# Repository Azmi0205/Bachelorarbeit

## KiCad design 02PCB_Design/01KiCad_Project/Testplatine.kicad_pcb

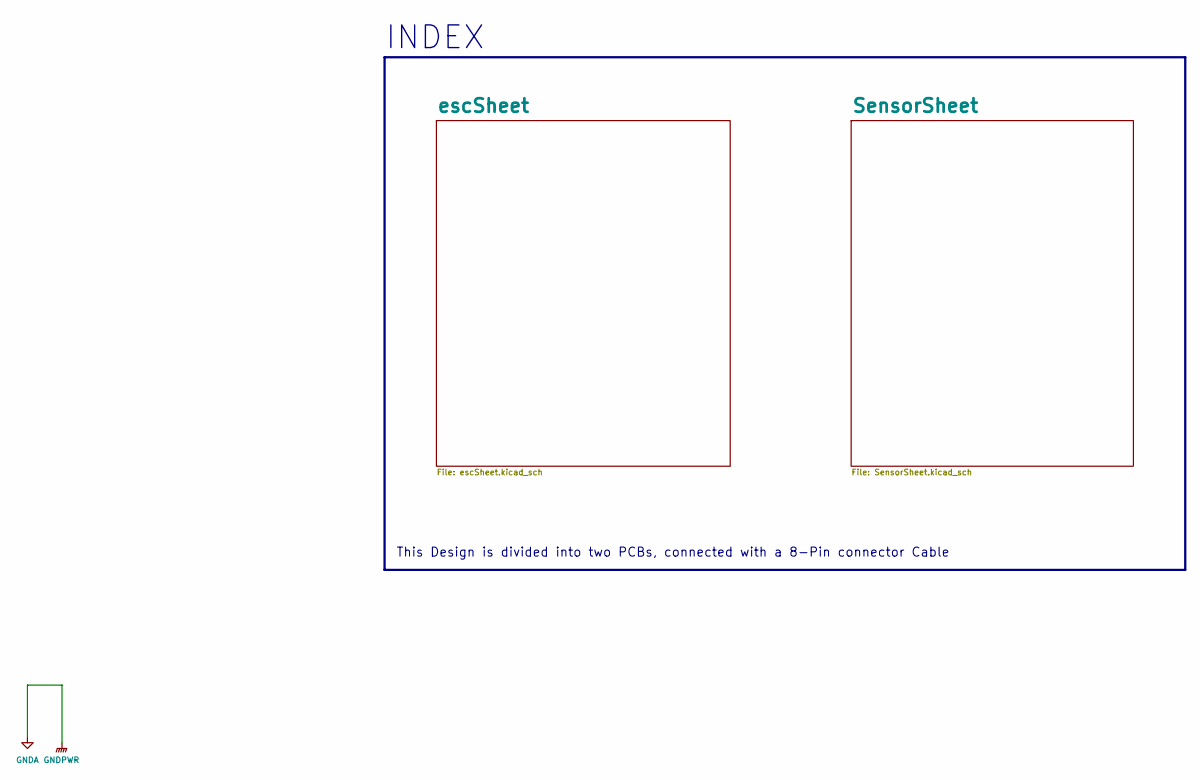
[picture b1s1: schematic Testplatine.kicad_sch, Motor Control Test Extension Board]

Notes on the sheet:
This Design is divided into two PCBs, connected with a 8-Pin connector Cable
INDEX

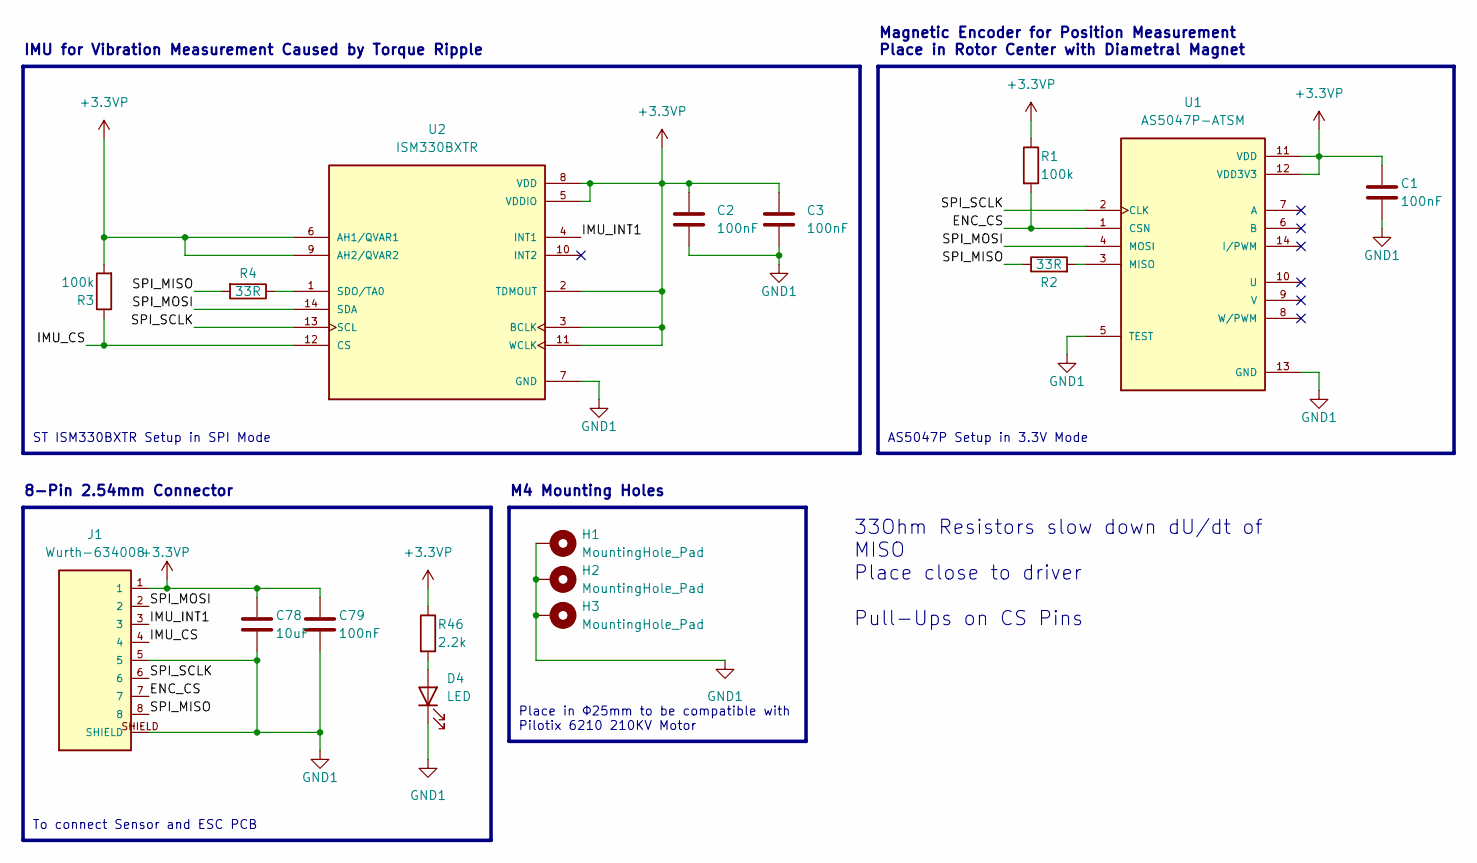
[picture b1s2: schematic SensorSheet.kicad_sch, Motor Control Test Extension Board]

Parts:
C1, C2, C3, C79: 100nF; C_0603_1608Metric_Pad1.08x0.95mm_HandSolder
C78: 10uF; C_1210_3225Metric_Pad1.33x2.70mm_HandSolder
D4: LED; LED_0805_2012Metric_Pad1.15x1.40mm_HandSolder
H1, H2, H3: MountingHole_Pad; MountingHole_4.3mm_M4_Pad_Via
J1: Wurth-634008; Wurth_634008_RJ45; PARTREV G
R1, R3: 100k; R_0603_1608Metric_Pad0.98x0.95mm_HandSolder
R2, R4: 33R; R_0603_1608Metric_Pad0.98x0.95mm_HandSolder
R46: 2.2k; R_0805_2012Metric_Pad1.20x1.40mm_HandSolder
U1: AS5047P-ATSM; TSSOP-14_4.4x5mm_P0.65mm; PARTREV 1-01
U2: ISM330BXTR; LGA-14_3x2.5mm_P0.5mm_LayoutBorder3x4y; PARTREV 2

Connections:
+3.3VP: C1.1, C2.1, C3.1, C78.1, C79.1, J1.1, R1.1, R3.2, R46.1, U1.11 (VDD), U1.12 (VDD3V3), U2.2 (TDMOUT), U2.3 (BCLK), U2.5 (VDDIO), U2.6 (AH1/QVAR1), U2.8 (VDD), U2.9 (AH2/QVAR2), U2.11 (WCLK)
/SensorSheet/ENC_CS: J1.7, R1.2, U1.1 (CSN)
/SensorSheet/IMU_CS: J1.4, R3.1, U2.12 (CS)
/SensorSheet/IMU_INT1: J1.3, U2.4 (INT1)
/SensorSheet/SPI_MISO: J1.8, R2.1, R4.2
/SensorSheet/SPI_MOSI: J1.2, U1.4 (MOSI), U2.14 (SDA)
/SensorSheet/SPI_SCLK: J1.6, U1.2 (CLK), U2.13 (SCL)
GND1: C1.2, C2.2, C3.2, C78.2, C79.2, D4.1 (K), H1.1, H2.1, H3.1, J1.5, J1.SHIELD, U1.5 (TEST), U1.13 (GND), U2.7 (GND)
unnamed: D4.2 (A), R46.2
unnamed: R2.2, U1.3 (MISO)
unnamed: R4.1, U2.1 (SDO/TA0)

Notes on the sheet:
33Ohm Resistors slow down dU/dt of MISO Place close to driver Pull-Ups on CS Pins
AS5047P Setup in 3.3V Mode
Place in Φ25mm to be compatible with Pilotix 6210 210KV Motor
8-Pin 2.54mm Connector
IMU for Vibration Measurement Caused by Torque Ripple
Magnetic Encoder for Position Measurement Place in Rotor Center with Diametral Magnet
To connect Sensor and ESC PCB
ST ISM330BXTR Setup in SPI Mode
M4 Mounting Holes

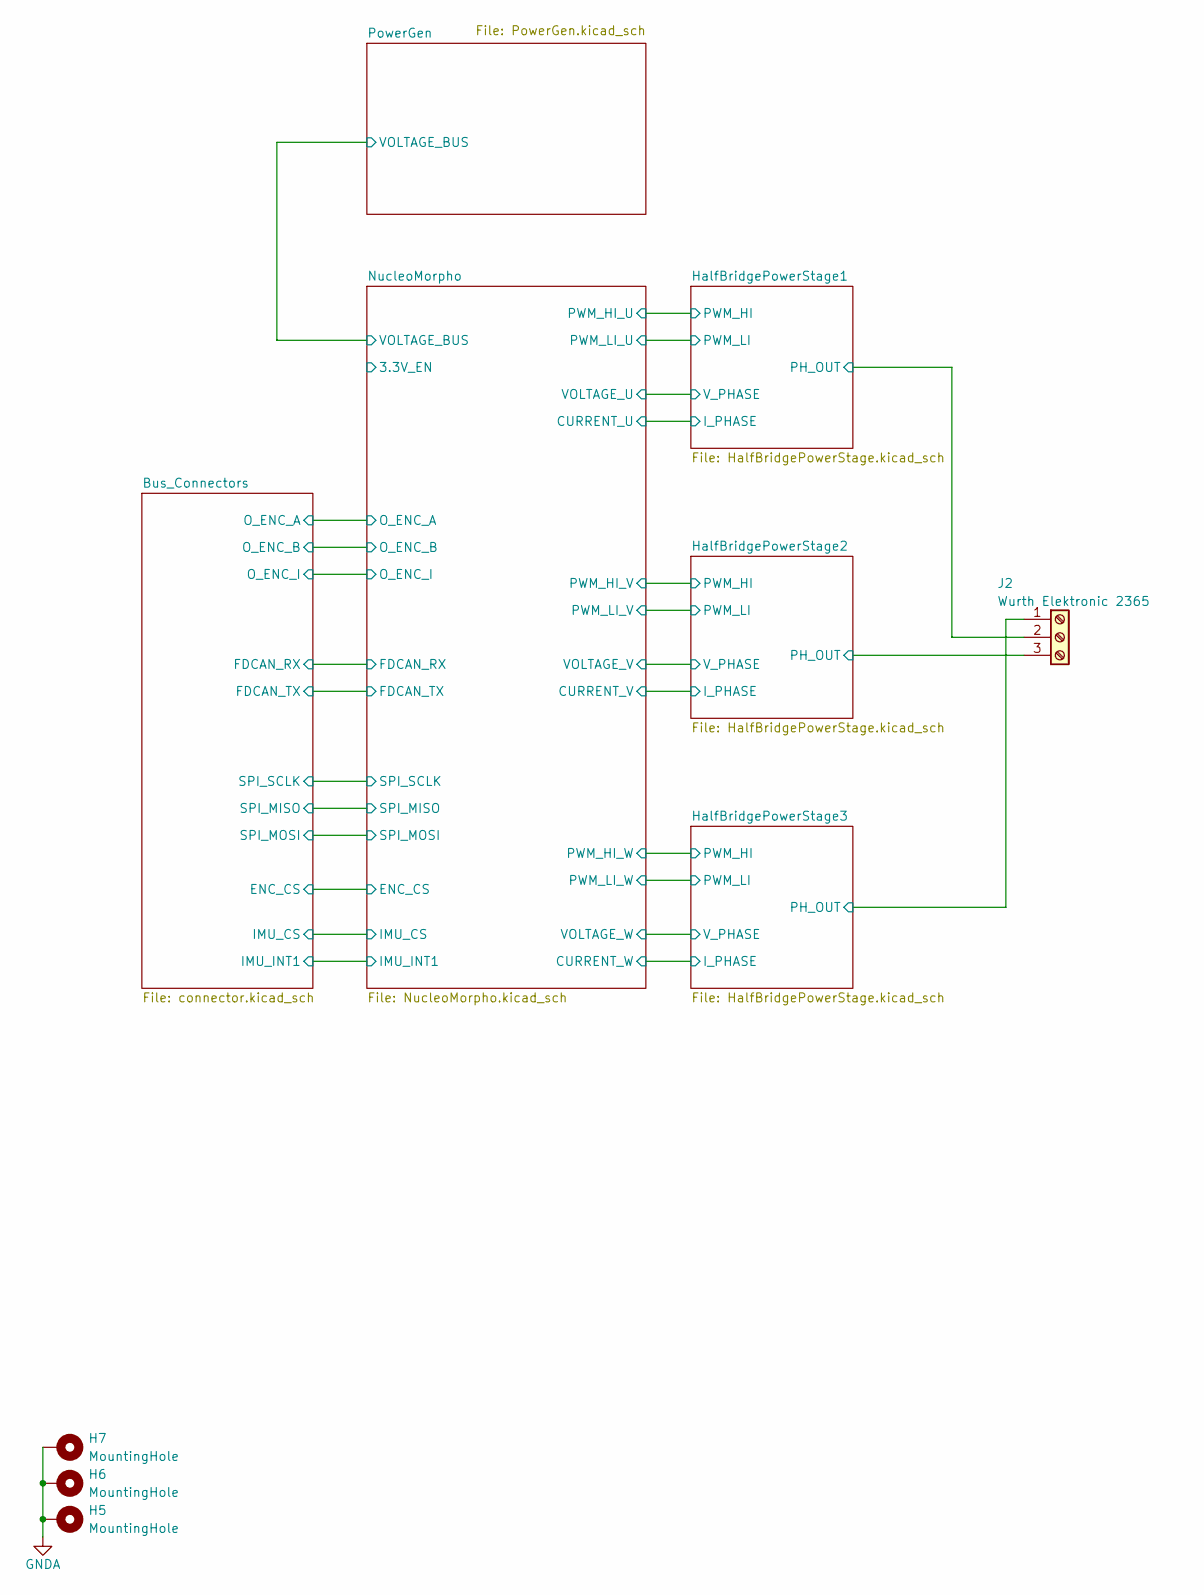
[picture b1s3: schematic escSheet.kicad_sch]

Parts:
H5, H6, H7: MountingHole; MountingHole_4.3mm_M4_Pad_Via
J2: Wurth Elektronic 2365; Wurth Elektronik 2365 Printklemme

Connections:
/escSheet/HalfBridgePowerStage1/PH_OUT: J2.2; also elsewhere on the board
/escSheet/HalfBridgePowerStage2/PH_OUT: J2.3; also elsewhere on the board
/escSheet/HalfBridgePowerStage3/PH_OUT: J2.1; also elsewhere on the board

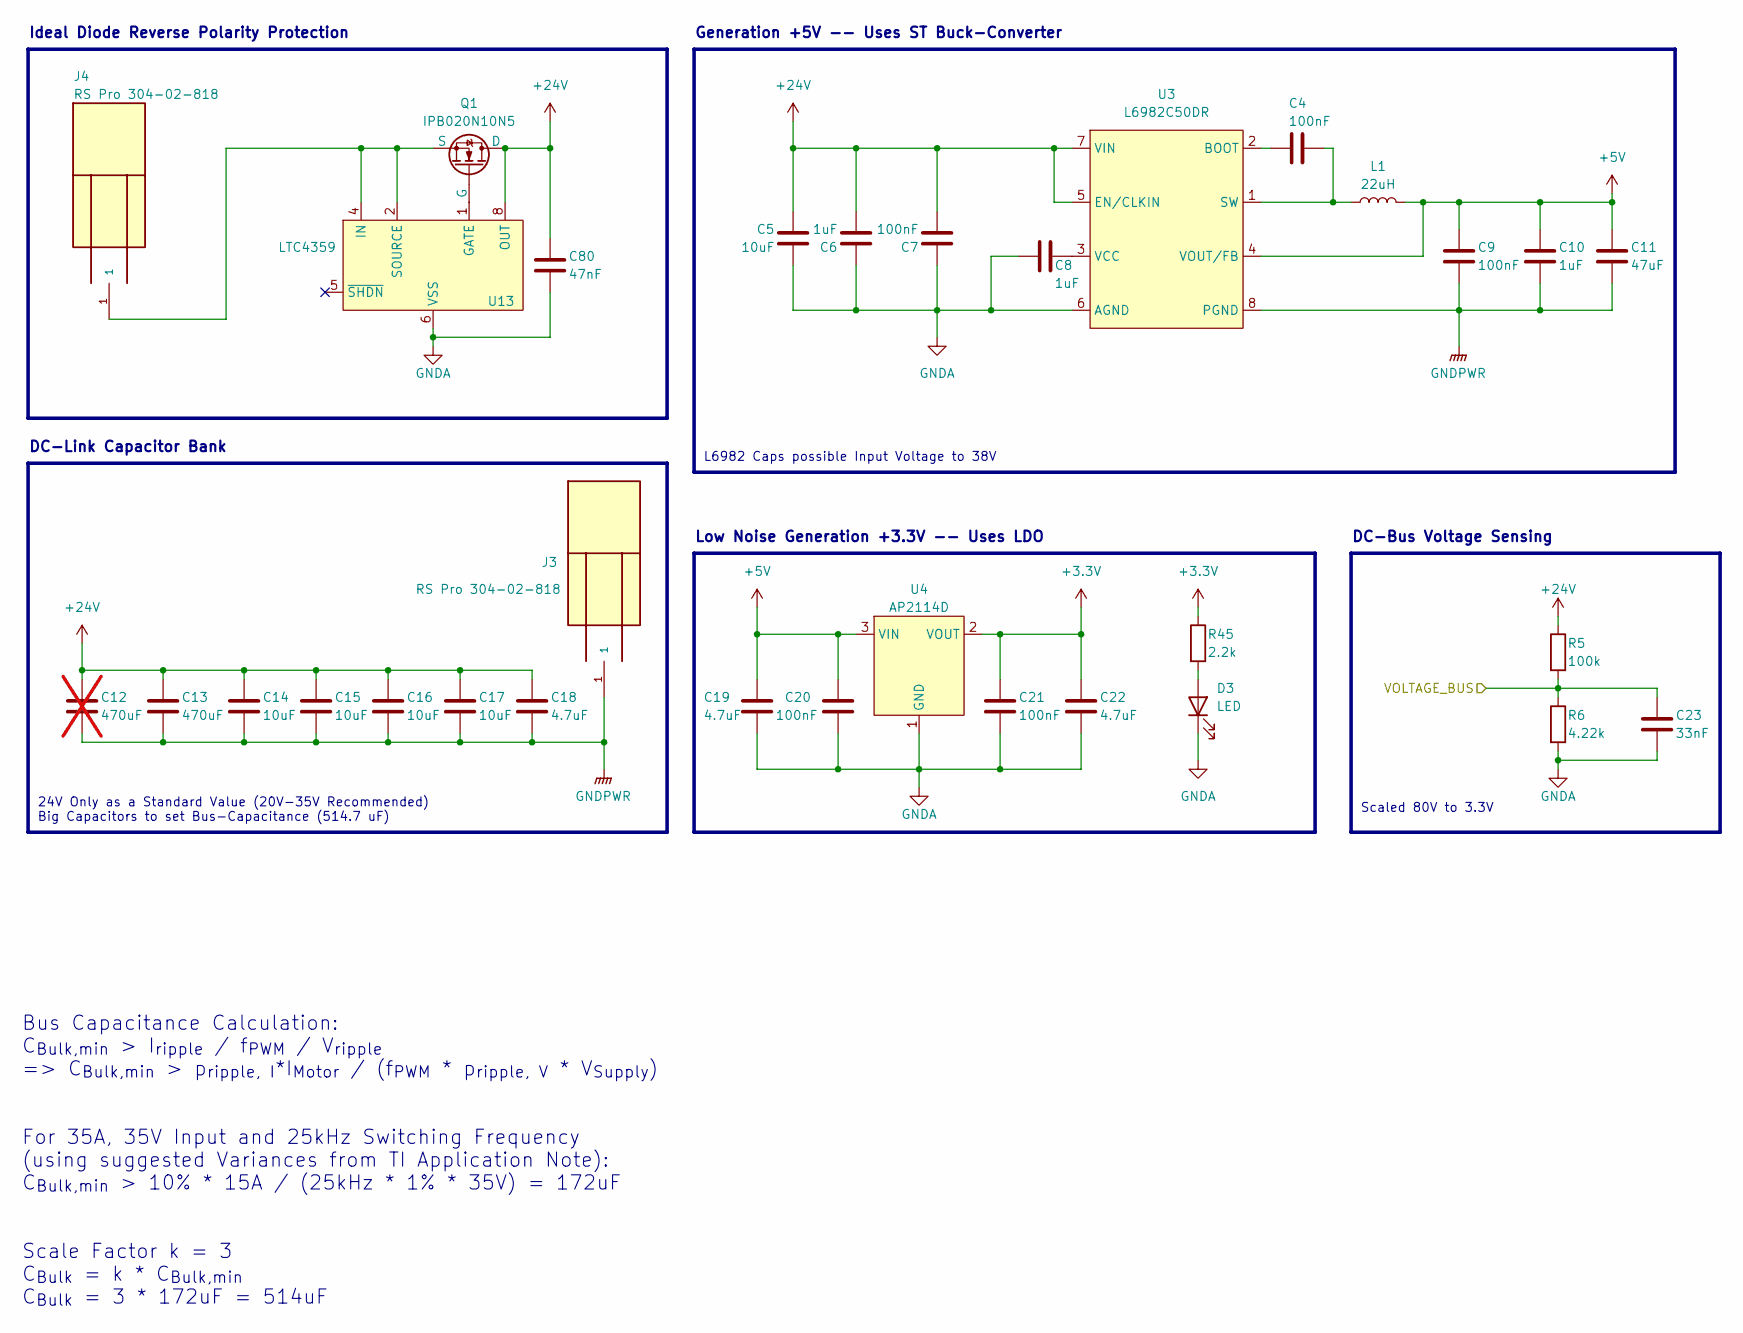
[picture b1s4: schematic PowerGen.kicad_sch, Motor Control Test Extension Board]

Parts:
C4, C7, C9, C20, C21: 100nF; C_0603_1608Metric_Pad1.08x0.95mm_HandSolder
C5, C14, C15, C16, C17: 10uF; C_1210_3225Metric_Pad1.33x2.70mm_HandSolder
C6, C8, C10: 1uF; C_0805_2012Metric_Pad1.18x1.45mm_HandSolder
C11: 47uF; C_1210_3225Metric_Pad1.33x2.70mm_HandSolder
C12: 470uF; CP_Radial_D16.0mm_P7.50mm; not fitted
C13: 470uF; CP_Radial_D16.0mm_P7.50mm
C18, C19, C22: 4.7uF; C_0805_2012Metric_Pad1.18x1.45mm_HandSolder
C23: 33nF; C_0603_1608Metric_Pad1.08x0.95mm_HandSolder
C80: 47nF; C_0603_1608Metric_Pad1.08x0.95mm_HandSolder
D3: LED; LED_0805_2012Metric_Pad1.15x1.40mm_HandSolder
J3, J4: RS Pro 304-02-818; FCR7350
L1: 22uH; L_Wuerth_MAPI-4020
Q1: IPB020N10N5; TO-263-2
R5: 100k; R_0603_1608Metric_Pad0.98x0.95mm_HandSolder
R6: 4.22k; R_0603_1608Metric_Pad0.98x0.95mm_HandSolder
R45: 2.2k; R_0805_2012Metric_Pad1.20x1.40mm_HandSolder
U3: L6982C50DR; SO-8_3.9x4.9mm_P1.27mm
U4: AP2114D; TO-252-2
U13: LTC4359; SO-8_3.9x4.9mm_P1.27mm

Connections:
+3.3V: C21.1, C22.1, R45.1, U4.2 (VOUT); also elsewhere on the board
+5V: C9.1, C10.1, C11.1, C19.1, C20.1, L1.2, U3.4 (VOUT/FB), U4.3 (VIN); also elsewhere on the board
+24V: C5.1, C6.2, C7.2, C12.1, C13.1, C14.1, C15.1, C16.1, C17.1, C18.1, C80.1, Q1.D, R5.1, U3.5 (EN/CLKIN), U3.7 (VIN), U13.8 (OUT); also elsewhere on the board
/escSheet/NucleoMorpho/VOLTAGE_BUS: C23.1, R5.2, R6.1; also elsewhere on the board
unnamed: D3.2 (A), R45.2
unnamed: C4.2, U3.2 (BOOT)
unnamed: C4.1, L1.1, U3.1 (SW)
unnamed: C8.1, U3.3 (VCC)
unnamed: Q1.G, U13.1 (GATE)
unnamed: J4.1, Q1.S, U13.2 (SOURCE), U13.4 (IN)

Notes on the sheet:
Bus Capacitance Calculation: C_{Bulk,min} > I_{ripple} / f_{PWM} / V_{ripple} => C_{Bulk,min} > p_{ripple, I}*I_{Motor} / (f_{PWM} * p_{ripple, V} * V_{Supply}) For 35A, 35V Input and 25kHz Switching Frequency (using suggested Variances from TI Application Note): C_{Bulk,min} > 10% * 15A / (25kHz *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
Scaled 80V to 3.3V
DC-Bus Voltage Sensing
Ideal Diode Reverse Polarity Protection
Low Noise Generation +3.3V -- Uses LDO
DC-Link Capacitor Bank
24V Only as a Standard Value (20V-35V Recommended) Big Capacitors to set Bus-Capacitance (514.7 uF)
L6982 Caps possible Input Voltage to 38V
Generation +5V -- Uses ST Buck-Converter

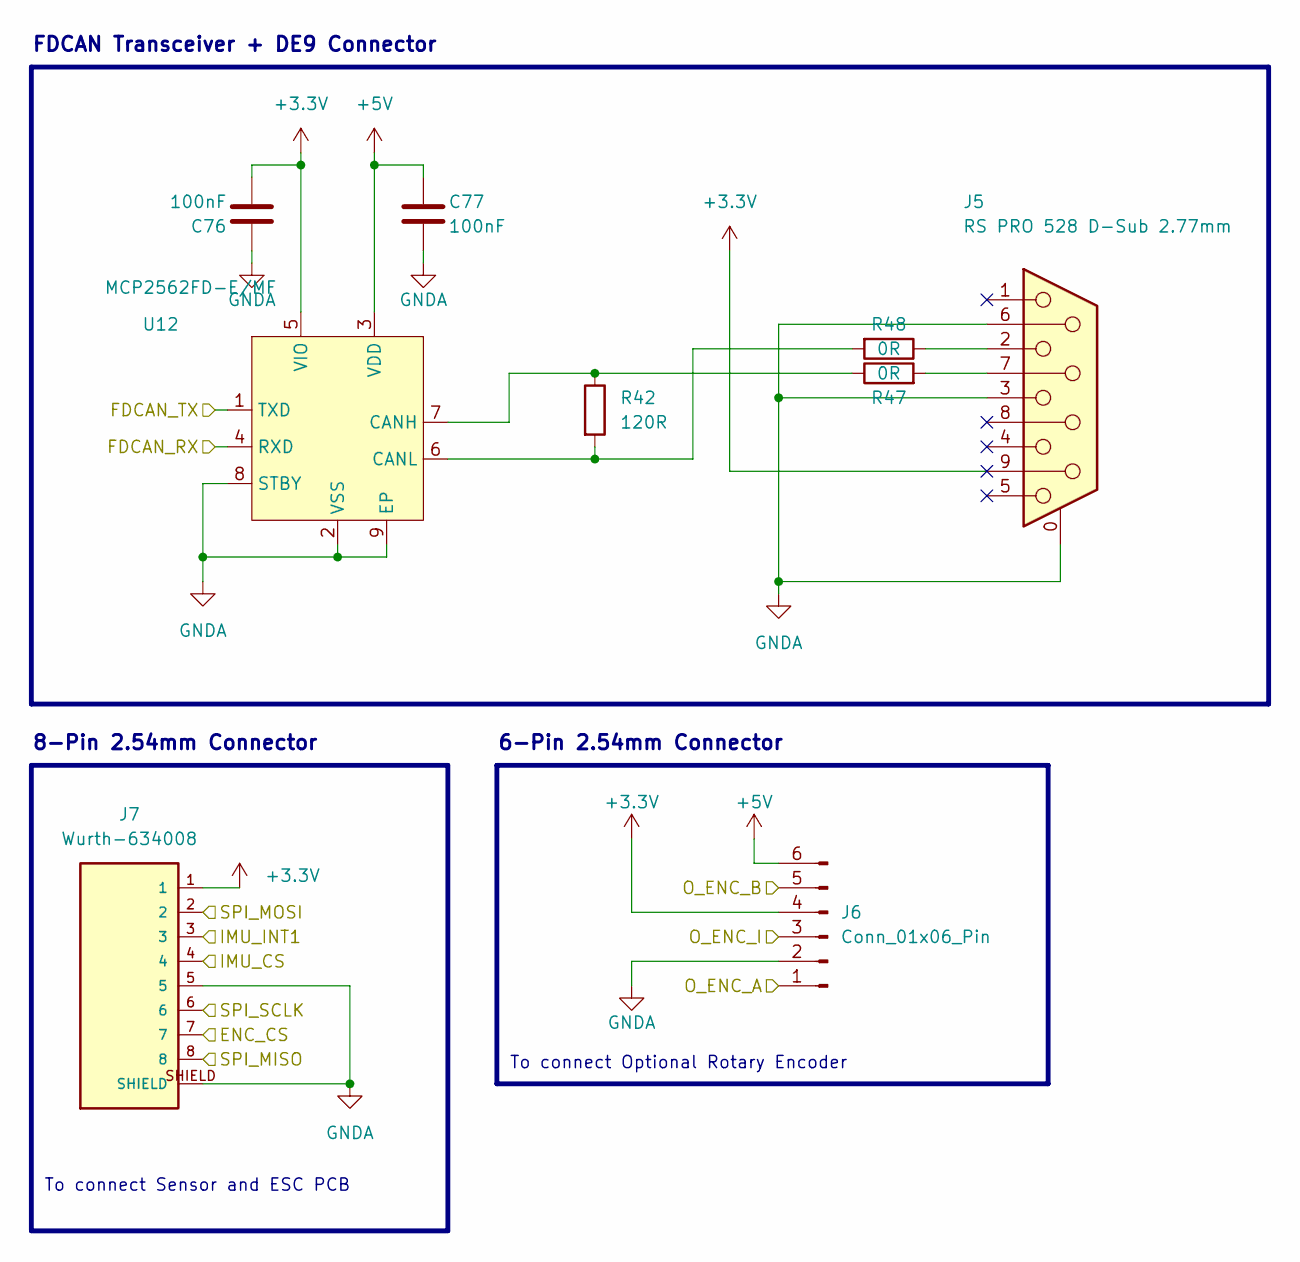
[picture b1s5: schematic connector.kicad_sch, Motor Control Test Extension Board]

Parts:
C76, C77: 100nF; C_0603_1608Metric_Pad1.08x0.95mm_HandSolder
J5: RS PRO 528 D-Sub 2.77mm; DSUB-9_Female_Horizontal_P2.77x2.84mm_EdgePinOffset4.94mm_H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
J6: Conn_01x06_Pin; PinHeader_2x03_P2.54mm_Horizontal
J7: Wurth-634008; Wurth_634008_RJ45; PARTREV G
R42: 120R; R_0603_1608Metric_Pad0.98x0.95mm_HandSolder
R47, R48: 0R; R_0603_1608Metric_Pad0.98x0.95mm_HandSolder
U12: MCP2562FD-E/MF; DFN-8-1EP_3x3mm_P0.65mm_EP1.55x2.4mm

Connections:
+3.3V: C76.2, J5.9, J6.4, J7.1, U12.5 (VIO); also elsewhere on the board
+5V: C77.1, J6.6, U12.3 (VDD); also elsewhere on the board
/escSheet/Bus_Connectors/ENC_CS: J7.7; also elsewhere on the board
/escSheet/Bus_Connectors/FDCAN_RX: U12.4 (RXD); also elsewhere on the board
/escSheet/Bus_Connectors/FDCAN_TX: U12.1 (TXD); also elsewhere on the board
/escSheet/Bus_Connectors/IMU_CS: J7.4; also elsewhere on the board
/escSheet/Bus_Connectors/IMU_INT1: J7.3; also elsewhere on the board
/escSheet/Bus_Connectors/O_ENC_A: J6.1; also elsewhere on the board
/escSheet/Bus_Connectors/O_ENC_B: J6.5; also elsewhere on the board
/escSheet/Bus_Connectors/O_ENC_I: J6.3; also elsewhere on the board
/escSheet/Bus_Connectors/SPI_MISO: J7.8; also elsewhere on the board
/escSheet/Bus_Connectors/SPI_MOSI: J7.2; also elsewhere on the board
/escSheet/Bus_Connectors/SPI_SCLK: J7.6; also elsewhere on the board
unnamed: J5.2, R48.1
unnamed: J5.7, R47.2
unnamed: R42.1, R47.1, U12.7 (CANH)
unnamed: R42.2, R48.2, U12.6 (CANL)

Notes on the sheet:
To connect Sensor and ESC PCB
FDCAN Transceiver + DE9 Connector
6-Pin 2.54mm Connector
To connect Optional Rotary Encoder
8-Pin 2.54mm Connector

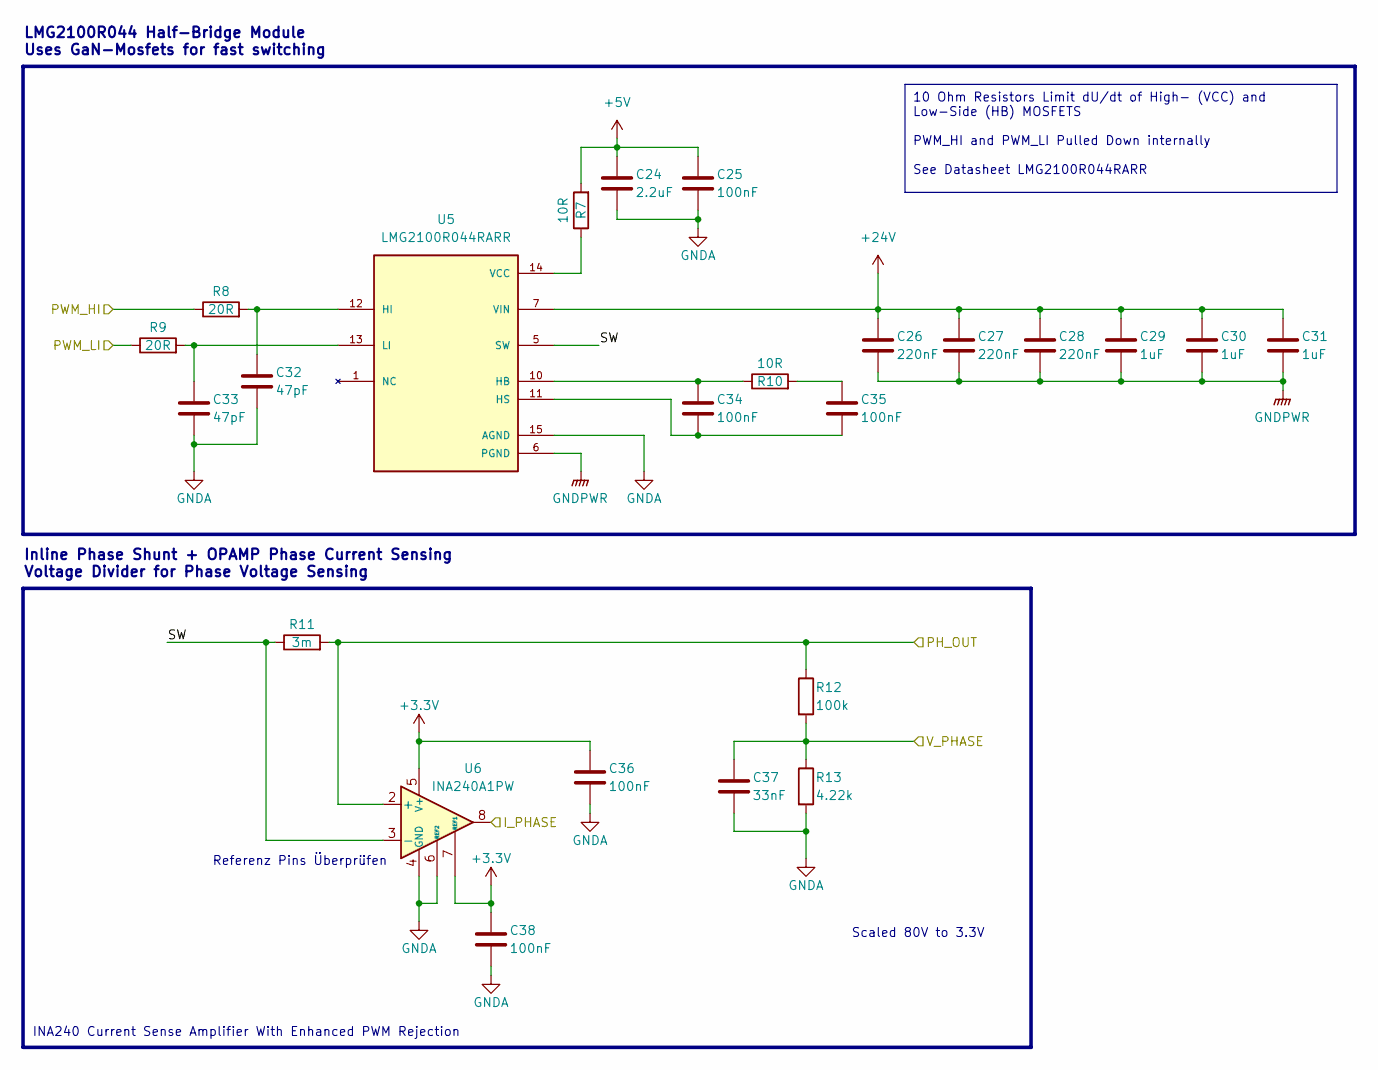
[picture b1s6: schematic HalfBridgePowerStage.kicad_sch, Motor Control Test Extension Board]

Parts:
C24: 2.2uF; C_0805_2012Metric_Pad1.18x1.45mm_HandSolder
C25, C34, C35, C36, C38: 100nF; C_0603_1608Metric_Pad1.08x0.95mm_HandSolder
C26, C27, C28: 220nF; C_0603_1608Metric_Pad1.08x0.95mm_HandSolder
C29, C30, C31: 1uF; C_0805_2012Metric_Pad1.18x1.45mm_HandSolder
C32, C33: 47pF; C_0603_1608Metric_Pad1.08x0.95mm_HandSolder
C37: 33nF; C_0603_1608Metric_Pad1.08x0.95mm_HandSolder
R7, R10: 10R; R_0603_1608Metric_Pad0.98x0.95mm_HandSolder
R8, R9: 20R; R_0603_1608Metric_Pad0.98x0.95mm_HandSolder
R11: 3m; R_2512_6332Metric_Pad1.40x3.35mm_HandSolder
R12: 100k; R_0603_1608Metric_Pad0.98x0.95mm_HandSolder
R13: 4.22k; R_0603_1608Metric_Pad0.98x0.95mm_HandSolder
U5: LMG2100R044RARR; RAR0016B-MFG; PARTREV B
U6: INA240A1PW; TSSOP-8_4.4x3mm_P0.65mm

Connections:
+3.3V: C36.1, C38.1, U6.5 (V+), U6.7 (REF1); also elsewhere on the board
+5V: C24.1, C25.1, R7.2; also elsewhere on the board
+24V: C26.1, C27.1, C28.1, C29.1, C30.1, C31.1, U5.7 (VIN); also elsewhere on the board
/escSheet/HalfBridgePowerStage1/I_PHASE: U6.8; also elsewhere on the board
/escSheet/HalfBridgePowerStage1/PH_OUT: R11.2, R12.1, U6.2 (+); also elsewhere on the board
/escSheet/HalfBridgePowerStage1/PWM_HI: R8.1; also elsewhere on the board
/escSheet/HalfBridgePowerStage1/PWM_LI: R9.1; also elsewhere on the board
/escSheet/HalfBridgePowerStage1/SW: R11.1, U5.5 (SW), U6.3 (-)
/escSheet/HalfBridgePowerStage1/V_PHASE: C37.1, R12.2, R13.1; also elsewhere on the board
unnamed: C35.1, R10.2
unnamed: C34.1, R10.1, U5.10 (HB)
unnamed: C32.1, R8.2, U5.12 (HI)
unnamed: C34.2, C35.2, U5.11 (HS)
unnamed: C33.1, R9.2, U5.13 (LI)
unnamed: R7.1, U5.14 (VCC)

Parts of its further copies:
C39, C54: 2.2uF; C_0805_2012Metric_Pad1.18x1.45mm_HandSolder
C40, C49, C50, C51, C53, C55, C64, C65, C66, C68: 100nF; C_0603_1608Metric_Pad1.08x0.95mm_HandSolder
C41, C42, C43, C56, C57, C58: 220nF; C_0603_1608Metric_Pad1.08x0.95mm_HandSolder
C44, C45, C46, C59, C60, C61: 1uF; C_0805_2012Metric_Pad1.18x1.45mm_HandSolder
C47, C48, C62, C63: 47pF; C_0603_1608Metric_Pad1.08x0.95mm_HandSolder
C52, C67: 33nF; C_0603_1608Metric_Pad1.08x0.95mm_HandSolder
R14, R17, R21, R24: 10R; R_0603_1608Metric_Pad0.98x0.95mm_HandSolder
R15, R16, R22, R23: 20R; R_0603_1608Metric_Pad0.98x0.95mm_HandSolder
R18, R25: 3m; R_2512_6332Metric_Pad1.40x3.35mm_HandSolder
R19, R26: 100k; R_0603_1608Metric_Pad0.98x0.95mm_HandSolder
R20, R27: 4.22k; R_0603_1608Metric_Pad0.98x0.95mm_HandSolder
U7, U9: LMG2100R044RARR; RAR0016B-MFG; PARTREV B
U8, U10: INA240A1PW; TSSOP-8_4.4x3mm_P0.65mm

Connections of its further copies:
+3.3V: C51.1, C53.1, C66.1, C68.1, U8.5 (V+), U8.7 (REF1), U10.5 (V+), U10.7 (REF1); also elsewhere on the board
+5V: C39.1, C40.1, C54.1, C55.1, R14.2, R21.2; also elsewhere on the board
+24V: C41.1, C42.1, C43.1, C44.1, C45.1, C46.1, C56.1, C57.1, C58.1, C59.1, C60.1, C61.1, U7.7 (VIN), U9.7 (VIN); also elsewhere on the board
/escSheet/HalfBridgePowerStage2/I_PHASE: U8.8; also elsewhere on the board
/escSheet/HalfBridgePowerStage2/PH_OUT: R18.2, R19.1, U8.2 (+); also elsewhere on the board
/escSheet/HalfBridgePowerStage2/PWM_HI: R15.1; also elsewhere on the board
/escSheet/HalfBridgePowerStage2/PWM_LI: R16.1; also elsewhere on the board
/escSheet/HalfBridgePowerStage2/SW: R18.1, U7.5 (SW), U8.3 (-)
/escSheet/HalfBridgePowerStage2/V_PHASE: C52.1, R19.2, R20.1; also elsewhere on the board
/escSheet/HalfBridgePowerStage3/I_PHASE: U10.8; also elsewhere on the board
/escSheet/HalfBridgePowerStage3/PH_OUT: R25.2, R26.1, U10.2 (+); also elsewhere on the board
/escSheet/HalfBridgePowerStage3/PWM_HI: R22.1; also elsewhere on the board
/escSheet/HalfBridgePowerStage3/PWM_LI: R23.1; also elsewhere on the board
/escSheet/HalfBridgePowerStage3/SW: R25.1, U9.5 (SW), U10.3 (-)
/escSheet/HalfBridgePowerStage3/V_PHASE: C67.1, R26.2, R27.1; also elsewhere on the board
unnamed: C50.1, R17.2
unnamed: C65.1, R24.2
unnamed: C49.1, R17.1, U7.10 (HB)
unnamed: C47.1, R15.2, U7.12 (HI)
unnamed: C49.2, C50.2, U7.11 (HS)
unnamed: C48.1, R16.2, U7.13 (LI)
unnamed: R14.1, U7.14 (VCC)
unnamed: C64.1, R24.1, U9.10 (HB)
unnamed: C62.1, R22.2, U9.12 (HI)
unnamed: C64.2, C65.2, U9.11 (HS)
unnamed: C63.1, R23.2, U9.13 (LI)
unnamed: R21.1, U9.14 (VCC)

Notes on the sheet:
10 Ohm Resistors Limit dU/dt of High- (VCC) and Low-Side (HB) MOSFETS PWM_HI and PWM_LI Pulled Down internally See Datasheet LMG2100R044RARR
LMG2100R044 Half-Bridge Module Uses GaN-Mosfets for fast switching
Scaled 80V to 3.3V
INA240 Current Sense Amplifier With Enhanced PWM Rejection
Referenz Pins Überprüfen
Inline Phase Shunt + OPAMP Phase Current Sensing Voltage Divider for Phase Voltage Sensing

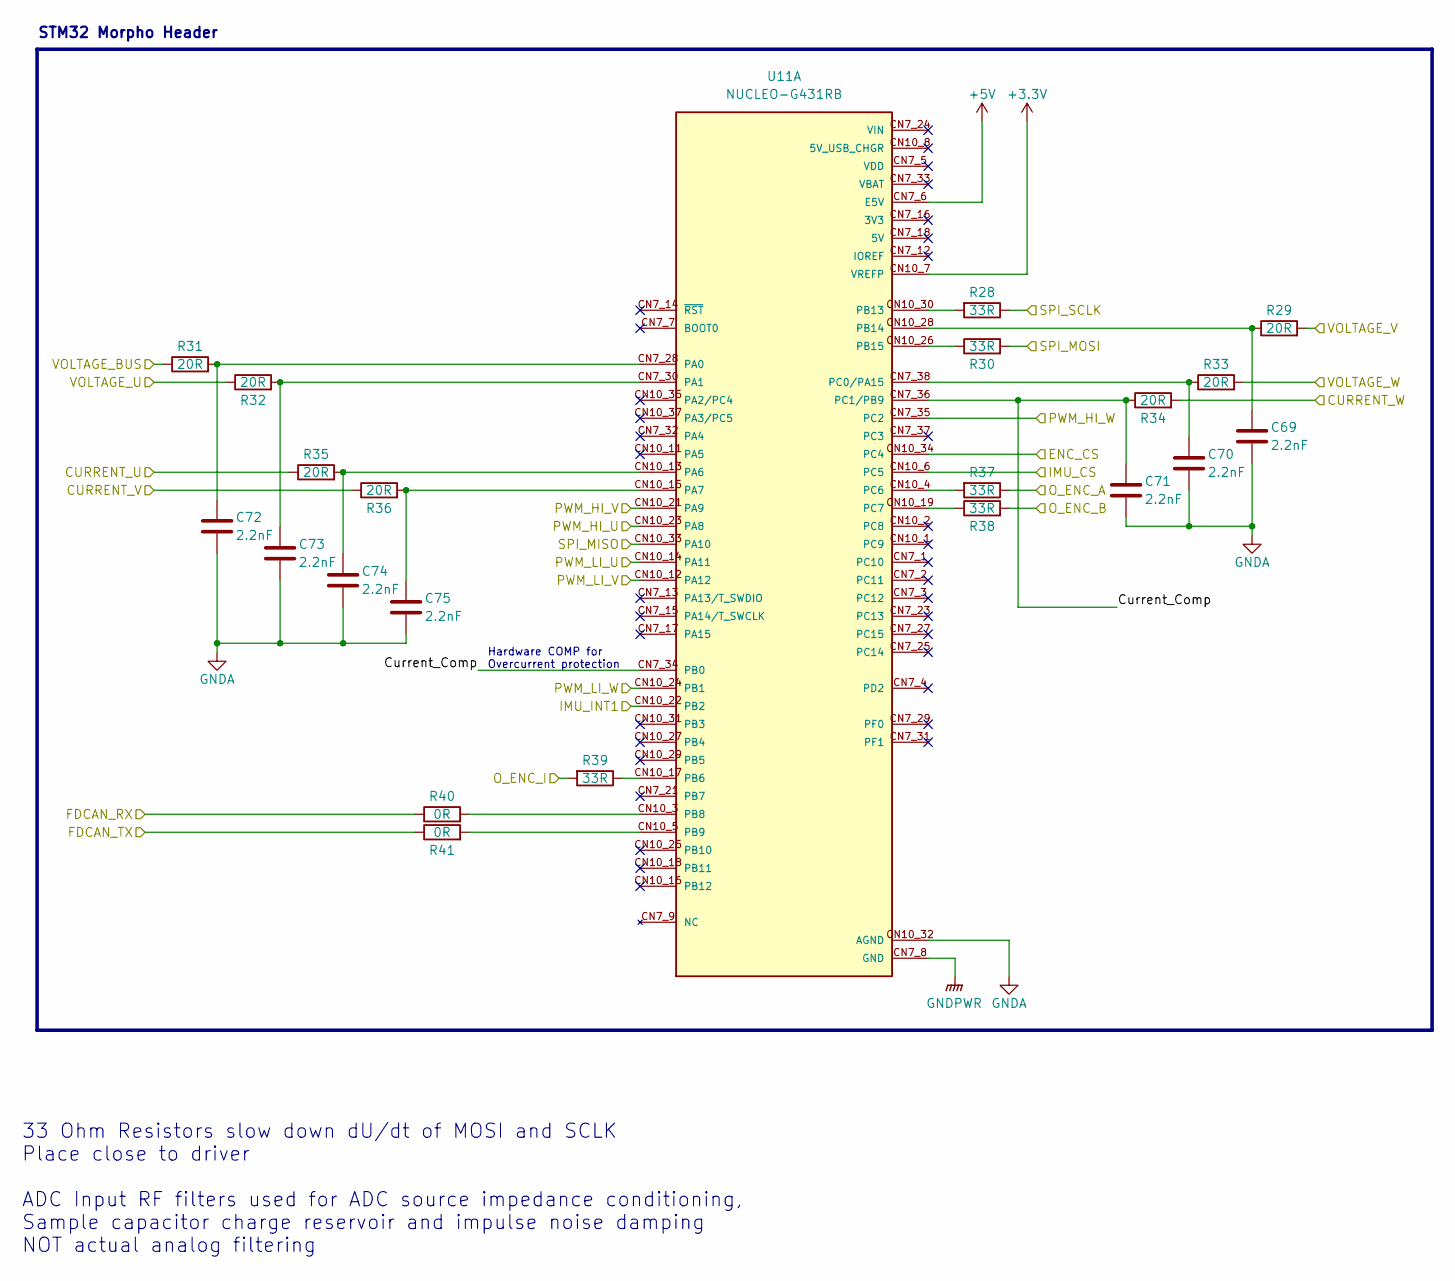
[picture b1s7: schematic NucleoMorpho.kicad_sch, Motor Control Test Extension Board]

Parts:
C69, C70, C71, C72, C73, C74, C75: 2.2nF; C_0603_1608Metric_Pad1.08x0.95mm_HandSolder
R28, R30, R37, R38, R39: 33R; R_0603_1608Metric_Pad0.98x0.95mm_HandSolder
R29, R31, R32, R33, R34, R35, R36: 20R; R_0603_1608Metric_Pad0.98x0.95mm_HandSolder
R40, R41: 0R; R_0603_1608Metric_Pad0.98x0.95mm_HandSolder
U11: NUCLEO-G431RB; NucleoCN7CN10; PARTREV 4

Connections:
+3.3V: U11.CN10_7 (VREFP); also elsewhere on the board
+5V: U11.CN7_6 (E5V); also elsewhere on the board
/escSheet/Bus_Connectors/ENC_CS: U11.CN10_34 (PC4); also elsewhere on the board
/escSheet/Bus_Connectors/FDCAN_RX: R40.1; also elsewhere on the board
/escSheet/Bus_Connectors/FDCAN_TX: R41.1; also elsewhere on the board
/escSheet/Bus_Connectors/IMU_CS: U11.CN10_6 (PC5); also elsewhere on the board
/escSheet/Bus_Connectors/IMU_INT1: U11.CN10_22 (PB2); also elsewhere on the board
/escSheet/Bus_Connectors/O_ENC_A: R37.1; also elsewhere on the board
/escSheet/Bus_Connectors/O_ENC_B: R38.2; also elsewhere on the board
/escSheet/Bus_Connectors/O_ENC_I: R39.2; also elsewhere on the board
/escSheet/Bus_Connectors/SPI_MISO: U11.CN10_33 (PA10); also elsewhere on the board
/escSheet/Bus_Connectors/SPI_MOSI: R30.2; also elsewhere on the board
/escSheet/Bus_Connectors/SPI_SCLK: R28.1; also elsewhere on the board
/escSheet/HalfBridgePowerStage1/I_PHASE: R35.1; also elsewhere on the board
/escSheet/HalfBridgePowerStage1/PWM_HI: U11.CN10_23 (PA8); also elsewhere on the board
/escSheet/HalfBridgePowerStage1/PWM_LI: U11.CN10_14 (PA11); also elsewhere on the board
/escSheet/HalfBridgePowerStage1/V_PHASE: R32.1; also elsewhere on the board
/escSheet/HalfBridgePowerStage2/I_PHASE: R36.1; also elsewhere on the board
/escSheet/HalfBridgePowerStage2/PWM_HI: U11.CN10_21 (PA9); also elsewhere on the board
/escSheet/HalfBridgePowerStage2/PWM_LI: U11.CN10_12 (PA12); also elsewhere on the board
/escSheet/HalfBridgePowerStage2/V_PHASE: R29.2; also elsewhere on the board
/escSheet/HalfBridgePowerStage3/I_PHASE: R34.2; also elsewhere on the board
/escSheet/HalfBridgePowerStage3/PWM_HI: U11.CN7_35 (PC2); also elsewhere on the board
/escSheet/HalfBridgePowerStage3/PWM_LI: U11.CN10_24 (PB1); also elsewhere on the board
/escSheet/HalfBridgePowerStage3/V_PHASE: R33.2; also elsewhere on the board
/escSheet/NucleoMorpho/3.3V_EN: U11.CN7_32 (PA4)
/escSheet/NucleoMorpho/Current_Comp: C71.1, R34.1, U11.CN7_34 (PB0), U11.CN7_36 (PC1/PB9)
/escSheet/NucleoMorpho/VOLTAGE_BUS: R31.1; also elsewhere on the board
unnamed: C72.1, R31.2, U11.CN7_28 (PA0)
unnamed: C73.1, R32.2, U11.CN7_30 (PA1)
unnamed: C74.1, R35.2, U11.CN10_13 (PA6)
unnamed: C75.1, R36.2, U11.CN10_15 (PA7)
unnamed: R39.1, U11.CN10_17 (PB6)
unnamed: R40.2, U11.CN10_3 (PB8)
unnamed: R41.2, U11.CN10_5 (PB9)
unnamed: R28.2, U11.CN10_30 (PB13)
unnamed: C69.1, R29.1, U11.CN10_28 (PB14)
unnamed: R30.1, U11.CN10_26 (PB15)
unnamed: C70.1, R33.1, U11.CN7_38 (PC0/PA15)
unnamed: R37.2, U11.CN10_4 (PC6)
unnamed: R38.1, U11.CN10_19 (PC7)

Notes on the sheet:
33 Ohm Resistors slow down dU/dt of MOSI and SCLK Place close to driver ADC Input RF filters used for ADC source impedance conditioning, Sample capacitor charge reservoir and impulse noise damping NOT actual analog filtering
STM32 Morpho Header
Hardware COMP for Overcurrent protection

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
